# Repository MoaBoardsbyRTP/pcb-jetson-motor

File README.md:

# pcb-jetson-motor
KiCAD PCB Project for the Interface board between the Jetson panel to the ESC motor driver

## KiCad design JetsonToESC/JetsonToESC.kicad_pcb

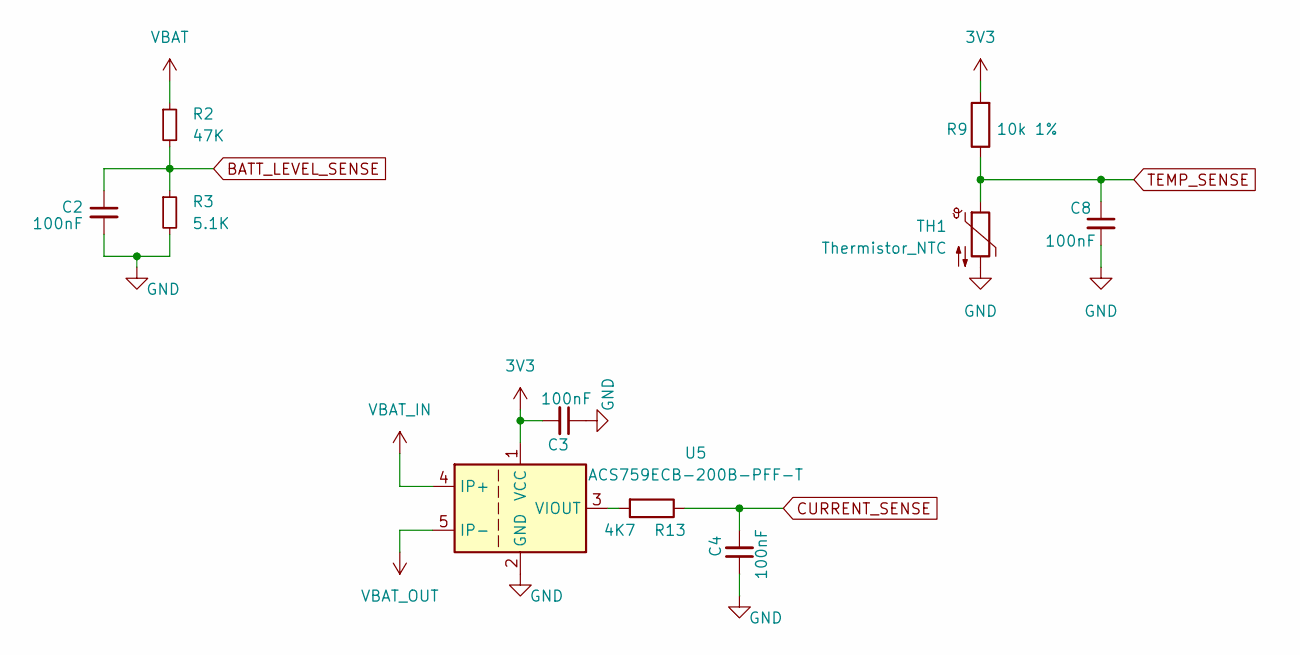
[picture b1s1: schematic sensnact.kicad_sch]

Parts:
C2, C8: 100nF; C_0603_1608Metric
C3, C4: 100nF; C_0805_2012Metric_Pad1.18x1.45mm_HandSolder
R2: 47K; R_0603_1608Metric
R3: 5.1K; R_0603_1608Metric
R9: 10k 1%; R_0603_1608Metric
R13: 4K7; R_0603_1608Metric
TH1: Thermistor_NTC; R_0805_2012Metric
U5: ACS759ECB-200B-PFF-T; Allegro_CB_PFF

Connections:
3V3: C3.2, R9.2, U5.1 (VCC); also elsewhere on the board
BATT_LEVEL_SENSE: C2.1, R2.2, R3.1; also elsewhere on the board
CURRENT_SENSE: C4.2, R13.1; also elsewhere on the board
GND: C2.2, C3.1, C4.1, C8.2, R3.2, TH1.2, U5.2 (GND); also elsewhere on the board
unnamed: R13.2, U5.3 (VIOUT)
TEMP_SENSE: C8.1, R9.1, TH1.1; also elsewhere on the board
VBAT: R2.1; also elsewhere on the board
VBAT_IN: U5.4 (IP+); also elsewhere on the board
VBAT_OUT: U5.5 (IP-); also elsewhere on the board

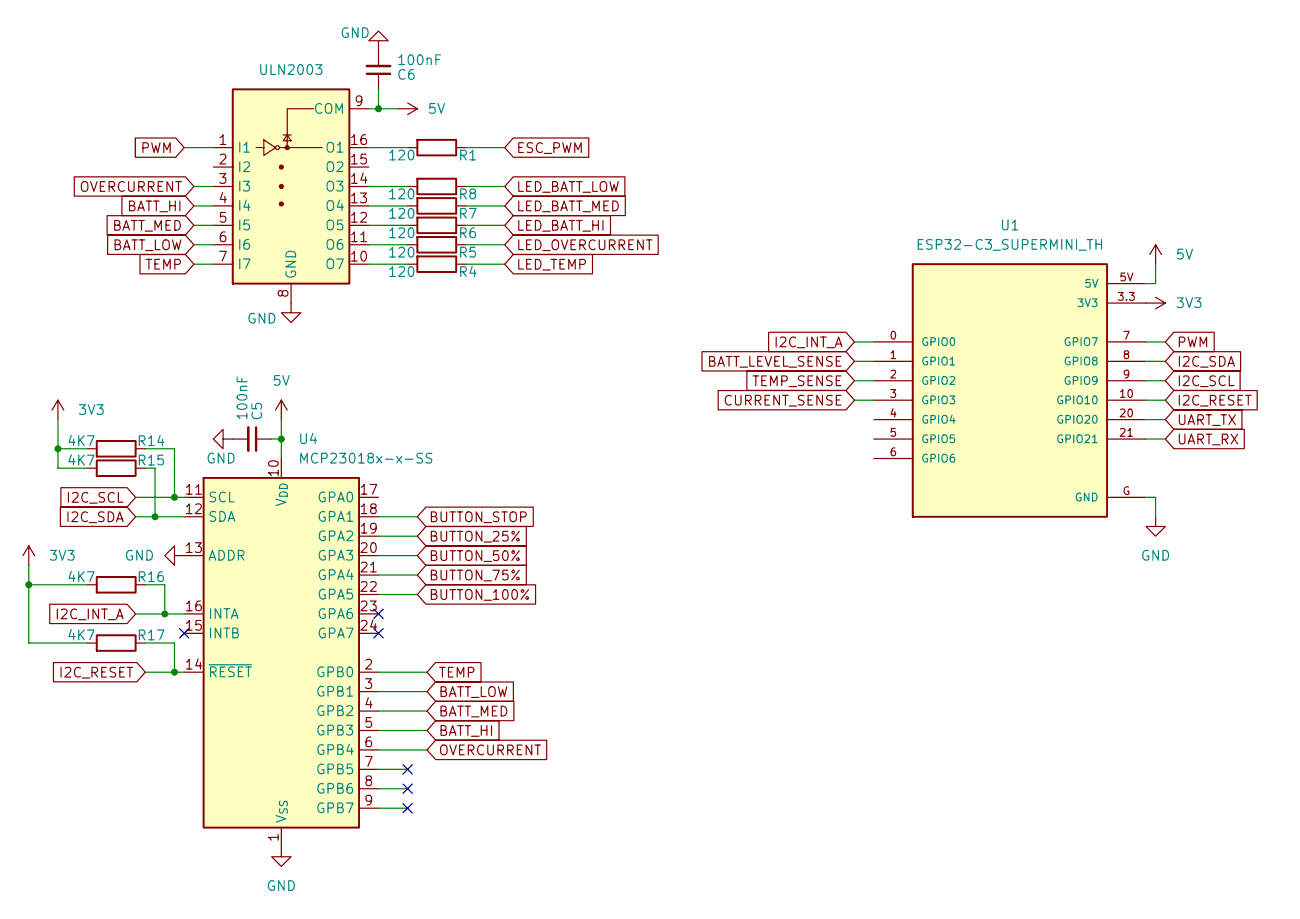
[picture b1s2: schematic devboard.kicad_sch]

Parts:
C5, C6: 100nF; C_0603_1608Metric
R1, R4, R5, R6, R7, R8: 120; R_0603_1608Metric
R14, R15, R16, R17: 4K7; R_0603_1608Metric
U1: ESP32-C3_SUPERMINI_TH; MODULE_ESP32-C3_SUPERMINI_TH
U4: MCP23018x-x-SS; SSOP-24_5.3x8.2mm_P0.65mm
U6: ULN2003; TSSOP-16_4.4x5mm_P0.65mm

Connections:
3V3: R14.2, R15.2, R16.2, R17.2, U1.3.3 (3V3); also elsewhere on the board
5V: C5.1, C6.1, U1.5V, U4.10 (V_{DD}), U6.9 (COM); also elsewhere on the board
BATT_HI: U4.5 (GPB3), U6.4 (I4)
BATT_LEVEL_SENSE: U1.1 (GPIO1); also elsewhere on the board
BATT_LOW: U4.3 (GPB1), U6.6 (I6)
BATT_MED: U4.4 (GPB2), U6.5 (I5)
BUTTON_25%: U4.19 (GPA2); also elsewhere on the board
BUTTON_50%: U4.20 (GPA3); also elsewhere on the board
BUTTON_75%: U4.21 (GPA4); also elsewhere on the board
BUTTON_100%: U4.22 (GPA5); also elsewhere on the board
BUTTON_STOP: U4.18 (GPA1); also elsewhere on the board
CURRENT_SENSE: U1.3 (GPIO3); also elsewhere on the board
ESC_PWM: R1.1; also elsewhere on the board
GND: C5.2, C6.2, U1.G (GND), U4.1 (V_{SS}), U4.13 (ADDR), U6.8 (GND); also elsewhere on the board
I2C_INT_A: R16.1, U1.0 (GPIO0), U4.16 (INTA)
I2C_RESET: R17.1, U1.10 (GPIO10), U4.14 (~RESET)
I2C_SCL: R14.1, U1.9 (GPIO9), U4.11 (SCL)
I2C_SDA: R15.1, U1.8 (GPIO8), U4.12 (SDA)
LED_BATT_HI: R6.1; also elsewhere on the board
LED_BATT_LOW: R8.1; also elsewhere on the board
LED_BATT_MED: R7.1; also elsewhere on the board
LED_OVERCURRENT: R5.1; also elsewhere on the board
LED_TEMP: R4.1; also elsewhere on the board
unnamed: R1.2, U6.16 (O1)
unnamed: R8.2, U6.14 (O3)
unnamed: R7.2, U6.13 (O4)
unnamed: R6.2, U6.12 (O5)
unnamed: R5.2, U6.11 (O6)
unnamed: R4.2, U6.10 (O7)
OVERCURRENT: U4.6 (GPB4), U6.3 (I3)
PWM: U1.7 (GPIO7), U6.1 (I1)
TEMP: U4.2 (GPB0), U6.7 (I7)
TEMP_SENSE: U1.2 (GPIO2); also elsewhere on the board
UART_RX: U1.21 (GPIO21)
UART_TX: U1.20 (GPIO20)

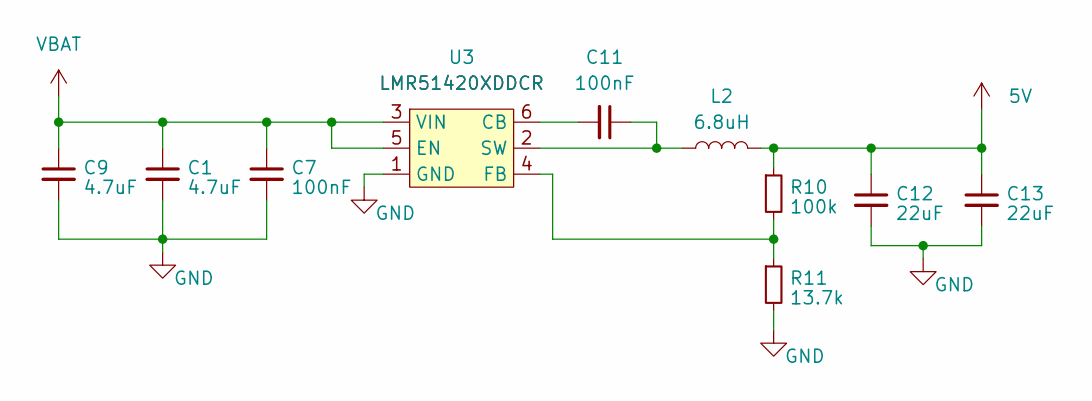
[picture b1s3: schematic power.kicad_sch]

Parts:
C1, C9: 4.7uF; C_1210_3225Metric_Pad1.33x2.70mm_HandSolder
C7, C11: 100nF; C_0603_1608Metric
C12, C13: 22uF; C_1210_3225Metric_Pad1.33x2.70mm_HandSolder
L2: 6.8uH; L_6.3x6.3_H3
R10: 100k; R_0805_2012Metric_Pad1.20x1.40mm_HandSolder
R11: 13.7k; R_0805_2012Metric_Pad1.20x1.40mm_HandSolder
U3: LMR51420XDDCR; SOT-23-6_Handsoldering

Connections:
5V: C12.1, C13.1, L2.2, R10.1; also elsewhere on the board
GND: C1.2, C7.2, C9.2, C12.2, C13.2, R11.2, U3.1 (GND); also elsewhere on the board
unnamed: C11.2, U3.6 (CB)
unnamed: R10.2, R11.1, U3.4 (FB)
unnamed: C11.1, L2.1, U3.2 (SW)
VBAT: C1.1, C7.1, C9.1, U3.3 (VIN), U3.5 (EN); also elsewhere on the board

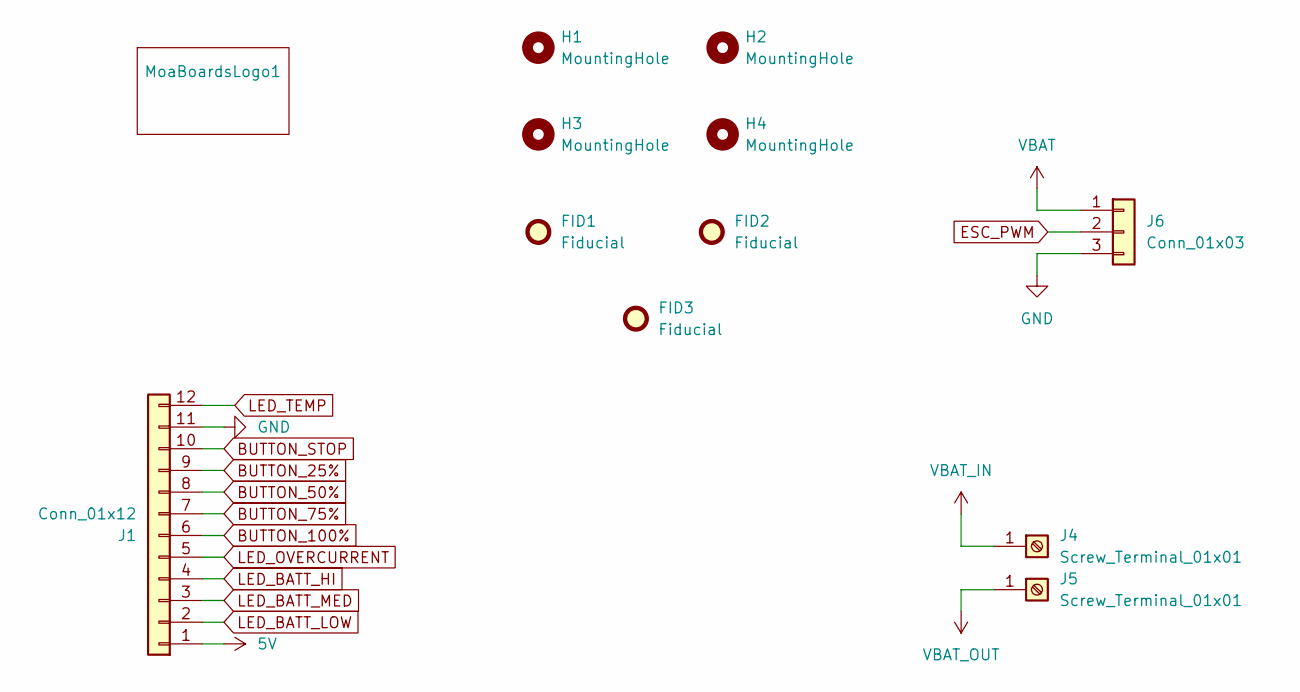
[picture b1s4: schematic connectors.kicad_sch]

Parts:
FID1, FID2, FID3: Fiducial; Fiducial_0.5mm_Mask1.5mm
H1, H2, H3, H4: MountingHole; TestPoint_Plated_Hole_D3.0mm
J1: Conn_01x12; IDC-Header_2x06_P2.54mm_Vertical
J4, J5: Screw_Terminal_01x01; MountingHole_4.3mm_M4_Pad_Via
J6: Conn_01x03; JST_XH_B3B-XH-A_1x03_P2.50mm_Vertical
MoaBoardsLogo1: MoaBoards

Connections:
5V: J1.1; also elsewhere on the board
BUTTON_25%: J1.9; also elsewhere on the board
BUTTON_50%: J1.8; also elsewhere on the board
BUTTON_75%: J1.7; also elsewhere on the board
BUTTON_100%: J1.6; also elsewhere on the board
BUTTON_STOP: J1.10; also elsewhere on the board
ESC_PWM: J6.2; also elsewhere on the board
GND: J1.11, J6.3; also elsewhere on the board
LED_BATT_HI: J1.4; also elsewhere on the board
LED_BATT_LOW: J1.2; also elsewhere on the board
LED_BATT_MED: J1.3; also elsewhere on the board
LED_OVERCURRENT: J1.5; also elsewhere on the board
LED_TEMP: J1.12; also elsewhere on the board
VBAT: J6.1; also elsewhere on the board
VBAT_IN: J4.1; also elsewhere on the board
VBAT_OUT: J5.1; also elsewhere on the board

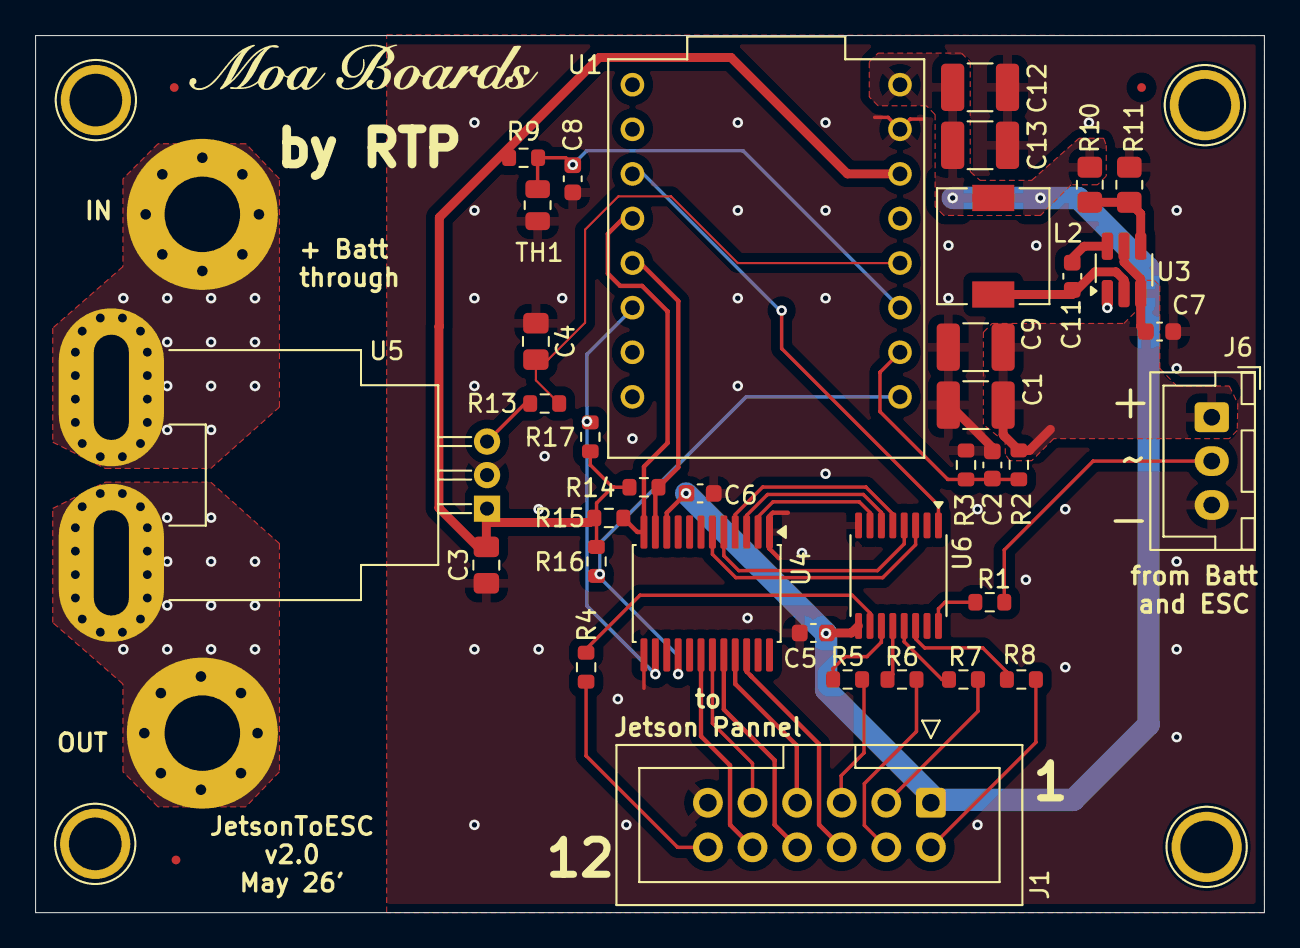
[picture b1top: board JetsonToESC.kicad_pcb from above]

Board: 2 copper layers, 70.0 x 50.0 mm, 47 parts (0 on the bottom side), 40 nets.

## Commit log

2026-01-13 Added footprints, connectors and cutout
2026-01-14 Added 3Dmodels
2026-01-14 Added mechanic drills
2026-01-16 Added most of components and preliminar routing
2026-01-19 Design almost finished, added hierarchical sheets
2026-01-19 Update design
2026-01-20 Start On this Branch
2026-01-20 Work on current sense and io expansion branch
2026-01-20 updated too
2026-01-21 Updated routing for IO Expander and Hall Sensor
2026-01-21 Edit around current sensor
2026-01-21 Update design and add 3d models
2026-01-22 Routed I2C pullups and Reset Added ESP32c3pinout image
2026-01-22 Design almost finished, added vias array for grounding too
2026-01-25 Design and routing done
2026-01-25 Fix on opto en output, now properly wired
2026-02-04 V_1.0.0: First version send to fabrication and assembly
2026-02-10 Rerouted current sense signal from GPIO5 (ADC2) to GPIO3(ADC1) to avoid errata on ESP32c3
2026-02-10 Added UART header
2026-03-20 Updated for v2.0, almost complete
2026-03-23 slight edit
2026-04-17 Changing connectors from JST to Generic male 2.54mm headers
2026-04-18 Changed connectors to headers and routed
2026-04-23 Edit mounting holes to 3mm
2026-05-07 Changed connectors into moles microfit
2026-05-07 updated before production
2026-05-07 Updated for Production
2026-05-20 Updated connector and temp sensor into IDC and NTC
